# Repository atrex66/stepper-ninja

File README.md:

# stepper-ninja

An open-source, free, high-performance step generator, digital I/O, and PWM interface for LinuxCNC and Mach3.

**NEW — first version of the 3-axis Mach3 driver (USB):**
[StepperNinja Mach3 USB package](configurations/StepperNinja-Mach3-USB).
Includes Pico/Pico 2 firmware, the Windows plugin, machine profiles, and
[setup instructions](configurations/StepperNinja-Mach3-USB/README.en.md).

A separate **prototype Mach3 driver** is available for a fixed three-axis USB/UDP
firmware profile. LinuxCNC remains the default profile with flexible configuration.

You definitely do not need the official breakout board to use stepper-ninja. A cheap printer-port breakout board is enough, and other configurations are also possible.

## Documentation

- [Installation Guide](docs/INSTALL.md)
- [Configuration Guide](docs/CONFIG.md)
- [IP Configuration Guide](docs/IPCONFIG.MD)
- [Make Your Own Breakout Board](docs/MAKE-YOUR-OWN-BREAKOUTBOARD.md)
- [Mach3 prototype overview](docs/MACH3.en.md) ([Magyar](docs/MACH3.hu.md))
- [Mach3 build guide](docs/MACH3-BUILD.en.md) ([Magyar](docs/MACH3-BUILD.hu.md))
- [Mach3 protocol and execution reports](docs/MACH3-PROTOCOL.en.md)
- [Mach3 Feed Hold and G31](docs/MACH3-FEEDHOLD-G31.en.md)

## Languages

- [English](README.md)
- [Deutsch](README.de.md)
- [हिन्दी](README.hi.md)
- [Magyar](README.hu.md)
- [Português (Brasil)](README.pt-BR.md)

## LinuxCNC features

LinuxCNC supports quadrature encoders and spindle-synchronized motion, including threading. Encoder support is not implemented in the Mach3 driver.

- **Supported configurations**:

  - W5100S-evb-pico UDP Ethernet. <https://docs.wiznet.io/Product/iEthernet/W5100S/w5100s-evb-pico>
  - W5500-evb-pico (same as above)
  - W5100S-evb-pico2 (same as above)
  - W5500-evb-pico2 (same as above)
  - pico + W5500 module (needs the same wiring as the W5100S-evb-pico)
  - pico2 + W5500 module (if you use a pico2 board with 48 GPIO, you can use the extra GPIO now)
  - pico + Raspberry Pi4 (uses direct SPI connection, tested with the official LinuxCNC ISO, utilizes the extra GPIO from the Pi 4)
  - pico2 + Raspberry Pi4 (same as above)
  - pico + PI ZERO2W (uses SPI connection, LinuxCNC runs with linuxcncrsh, tested on Bookworm with patched kernel 6.13.2.5-rt5-v7+)
  - pico2 + PI ZERO2W (same as above, able to use the extra GPIO from the ZERO2W)
  - Stepper Ninja official breakout board (needs a pico and a W5500 module)

- **Using with single board compiters (SBC) and SPI**:
  - the stepper-ninja project now uses the kernel spi drivers and libgpiod v2 for communication, a littlebit slower
  - than the bmc2835 driver but with this change in theory no more barrier to use another SBC (single board computer) 

- **Breakout-board v1.0 - Digital version**: 16 optically isolated inputs, 8 optically isolated outputs, 4 step generators (differential output), 2 high-speed encoder inputs, 2 12-bit DAC outputs (unipolar).

- **step-generator**: max 8 with pico 1, max 12 with pico2. 1 MHz per channel. Pulse width is set from a HAL pin (96 ns - 6300 ns with a 125 MHz pico, 60 ns - 4000 ns with a 200 MHz pico).

- **quadrature-encoder**: max 8 with pico1, max 12 with pico2. High speed, zero-pulse handling, velocity estimation for low-resolution encoders, and spindle-synchronized motion support.

- **digital I/O**: you can configure the free pins of the pico as inputs and outputs.

- **PWM**: you can configure up to 16 GPIOs for PWM output (1900 Hz with 16-bit resolution up to 1 MHz with 7-bit resolution), and you can choose active-low or active-high behavior.

- **Software**:
  - LinuxCNC HAL driver supporting multiple instances (max 4), with safety functions (timeout, data checks).

- **extra I/O**: the I/O expander for the breakout board supports up to 64 inputs and 32 outputs total (with 3 expanders, 24 V optically isolated).

- **user breakout board code**: breakoutboard_user.c and breakoutboard_hal_user.c were added to the modules directory for makers to make integration easier.

- **sample KiCad breakout board**: a simple, low-cost DIY breakout board KiCad project is available in `configurations/RaspberryPi`. It connects a Pico/Pico2 to a Raspberry Pi via SPI and requires only a Pico or Pico2, a standard 40-pin GPIO header, and 2.54 mm PCB screw terminals.

- **supporters**: all active sponsors at or above $15 get access to the private breakout board repository for personal use, including production files such as Gerbers, BOM, and component positions.

- **Open-Source**: code and docs under MIT License.

## Mach3 prototype driver

The `mach3-driver/` directory contains a Mach3 SDK adapter and a portable
controller/client core. Select `STEPPER_NINJA_PROFILE=mach3-3axis` when building
the matching firmware. This profile has a fixed pinout: three STEP/DIR axes,
seven digital inputs, six digital outputs, and one spindle PWM output.

Implemented in the prototype:

- Buffered 1 ms XYZ motion and execution reports from physical STEP counts.
- Local acceleration-limited jog, homing, and dwell.
- Digital I/O, spindle RUN/DIR/PWM, and coolant outputs.
- Sessions, ACKs, duplicate-request suppression, watchdog, E-stop and limit handling.
- A Mach3 configuration dialog for IP/port, timing, polarity, and homing settings.
- Native Mach3 Feed Hold forwarding the planned braking trajectory; Cycle Start
  forwards Mach3's new startup trajectory.
- Coordinated G31 with separate contact and stopping positions, missed-contact
  detection, and controlled cancellation.

**Prototype status:** portable Linux tests cover motion, reports, and UDP behavior;
these use a substitute Mach3 planner. I have verified on Windows that USB STEP outputs and inputs work from Mach3 with the prebuilt driver and firmware.
Full Mach3 Feed Hold/G31 integration and hardware timing still need validation.
USB CDC motion transport is implemented with automatic console handover; full
Windows and physical machine validation remain pending. The Mach3 profile has no encoder; the LinuxCNC
performance and configuration features listed above do not describe its limits.
Motion protocol version 3 requires matching Mach3 driver and firmware builds.
The Pico firmware can also be built natively on Windows; no Linux machine is
required to build the firmware and Mach3 DLL. Once real Mach3 and hardware
testing has confirmed reliable operation, a release is planned with prebuilt
firmware and driver binaries. That validated release is not available yet.

[Mach3 USB configuration directory — prebuilt driver, firmware, and machine profiles](configurations/StepperNinja-Mach3-USB).

See the [English build guide](docs/MACH3-BUILD.en.md) or
[Hungarian build guide](docs/MACH3-BUILD.hu.md). The separate Mach3 profile
preserves LinuxCNC's existing flexible configuration and protocol.

## Contributors

The LinuxCNC 2.9/2.10 HAL API compatibility patch is based on code by [Frederic Müller (FredericM88)](https://github.com/FredericM88) in [linuxcnc-sim](https://github.com/FredericM88/linuxcnc-sim/tree/42ef3723da83b8ed88c123138c60437093255a22/compat/stepper-ninja), adapted for this driver under the MIT license. See the [compatibility notes](hal-driver/hal-api-compatibility.md) and [original license](hal-driver/LICENSE.hal-compat.txt).

- **code**: atrex66, pippin88

- **testing**: Jimfong1, Griletos

- **supporters**: Griletos, Cofhal, Sunhapas, milhead2, vanOverload

- **known-ninjas**: Griletos, Cofhal, Sunhapas, milhead2, vanOverload, Player

## Discord

- Request a fresh Discord invite in Discussions.

## License

- The quadrature encoder PIO program uses BSD-3 license by Raspberry Pi (Trading) Ltd.
- The `ioLibrary_Driver` is licensed under the MIT License by Wiznet.

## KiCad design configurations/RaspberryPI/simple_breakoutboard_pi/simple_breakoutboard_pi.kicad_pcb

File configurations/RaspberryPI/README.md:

# Installation and Build Instructions for Stepper-Ninja (Raspberry Pi SPI)

This guide explains how to build **Stepper-Ninja** and the LinuxCNC HAL driver for Raspberry Pi Pico/Pico2 connected via **SPI** to a Raspberry Pi 4/5.

This version uses the **kernel SPI driver** (`spidev`) and **libgpiod v2** for communication — no bcm2835 library required.

Tested with Pico SDK 2.1.1, CMake 3.20.6, and GNU ARM Embedded Toolchain. See [Troubleshooting](#troubleshooting) for common issues.

---

## Prerequisites

Before building, install the following dependencies:

```bash
sudo apt update
sudo apt install cmake gcc-arm-none-eabi binutils-arm-none-eabi \
                 build-essential unzip libgpiod-dev
```

**Pico SDK (2.1.1)**:

```bash
git clone https://github.com/raspberrypi/pico-sdk
cd pico-sdk
git submodule update --init
export PICO_SDK_PATH=/path/to/pico-sdk
```

Add `PICO_SDK_PATH` to your shell profile (e.g., `~/.bashrc`).

---

## Cloning the Repository

```bash
git clone https://github.com/atrex66/stepper-ninja
cd stepper-ninja
```

---

## Raspberry Pi SPI Setup

Enable SPI in `/boot/firmware/config.txt`:

```
dtparam=spi=on
```

> **Note:** The previous bcm2835-based version required `spi=off`. This version uses the kernel `spidev` driver — SPI **must be enabled**.

---

## Building with CMake and Make

### 1. Copy the Raspberry Pi configuration

```bash
cd ~/stepper-ninja
cp configurations/RaspberryPI/config.h firmware/inc/
```

### 2. Create a Build Directory

```bash
cd firmware/
mkdir build && cd build
```

### 3. Configure CMake

- For **Pico**:

  ```bash
  cmake ..
  ```

- For **Pico2**:

  ```bash
  cmake -DBOARD=pico2 ..
  ```

### 4. Build the Project

```bash
make
```

This generates `stepper-ninja-picoX.uf2`.

### 5. Flash the Pico

- Connect the Pico in BOOTSEL mode (hold BOOTSEL, plug in USB).
- If you are using the pico with other firmware use flash_nuke to erase previous data from the flash memory.
- Copy the `.uf2` file to the Pico's mass storage device.
- The Pico reboots and runs the firmware.

---

### 6. Build the HAL driver

 - go to __~/stepper-ninja/hal-driver__
 - run __./install.sh__ or __./rip_install.sh__ depending on your LinuxCNC installation

## Pico2 Support

For a Pico2, ensure:

- The Raspberry Pi is properly wired (SPI pins, INT pin, power).
- Use `-DBOARD=pico2` in the CMake step.

## Installing the LinuxCNC HAL Driver

To integrate Stepper-Ninja with LinuxCNC:

1. **Install the HAL Driver**:

   ```bash
   cd hal-driver
   ./install.sh
   ```

2. **Create a HAL File** (e.g., `stepper-ninja.hal`):

   ```hal
   loadrt stepgen-ninja

   addf stepgen-ninja.0.watchdog-process servo-thread
   addf stepgen-ninja.0.process-send servo-thread
   addf stepgen-ninja.0.process-recv servo-thread

   net x-pos-cmd joint.0.motor-pos-cmd => stepgen-ninja.0.stepgen.0.command
   net x-pos-fb stepgen-ninja.0.stepgen.0.feedback => joint.0.motor-pos-fb
   net x-enable axis.0.amp-enable-out => stepgen-ninja.0.stepgen.0.enable
   ```

3. **Update the INI File** (e.g., `your_config.ini`):

   ```ini
   [HAL]
   HALFILE = stepper-ninja.hal

   [EMC]
   SERVO_PERIOD = 1000000
   ```

4. **Run LinuxCNC**:

   ```bash
   linuxcnc your_config.ini
   ```

---

## Troubleshooting

- **CMake Error: PICO_SDK_PATH not found**:
  Ensure `PICO_SDK_PATH` is set and points to the Pico SDK directory.
  
  ```bash
  export PICO_SDK_PATH=/path/to/pico-sdk
  ```

- **Missing pioasm/elf2uf2**:
  Build these tools in the Pico SDK:
  
  ```bash
  cd pico-sdk/tools/pioasm
  mkdir build && cd build
  cmake .. && make
  ```

- **UTF-8 BOM Errors** (e.g., `∩╗┐` in linker output):
  Use CMake 3.20.6 or add `-DCMAKE_UTF8_BOM=OFF`:
  
  ```bash
  cmake -DCMAKE_UTF8_BOM=OFF ..
  ```

- **HAL Driver Errors**:
  Check `dmesg` for UDP connection issues:
  
  ```bash
  dmesg | grep stepgen-ninja
  ```

For more help, share error logs on the [GitHub Issues page](https://github.com/atrex66/stepper-ninja/issues) or the [Reddit thread](https://www.reddit.com/r/hobbycnc/comments/1koomzu/).

---

## Community Notes

Thanks to the r/hobbycnc community for testing! Stepper-Ninja v1.0 is tagged as a stable release: <https://github.com/atrex66/stepper-ninja/releases/tag/v1.0>

This version switches from bcm2835 to kernel SPI (`spidev`) and libgpiod v2, making it compatible with a wider range of SBCs in the future.

For more information, see the main [README](../../README.md).

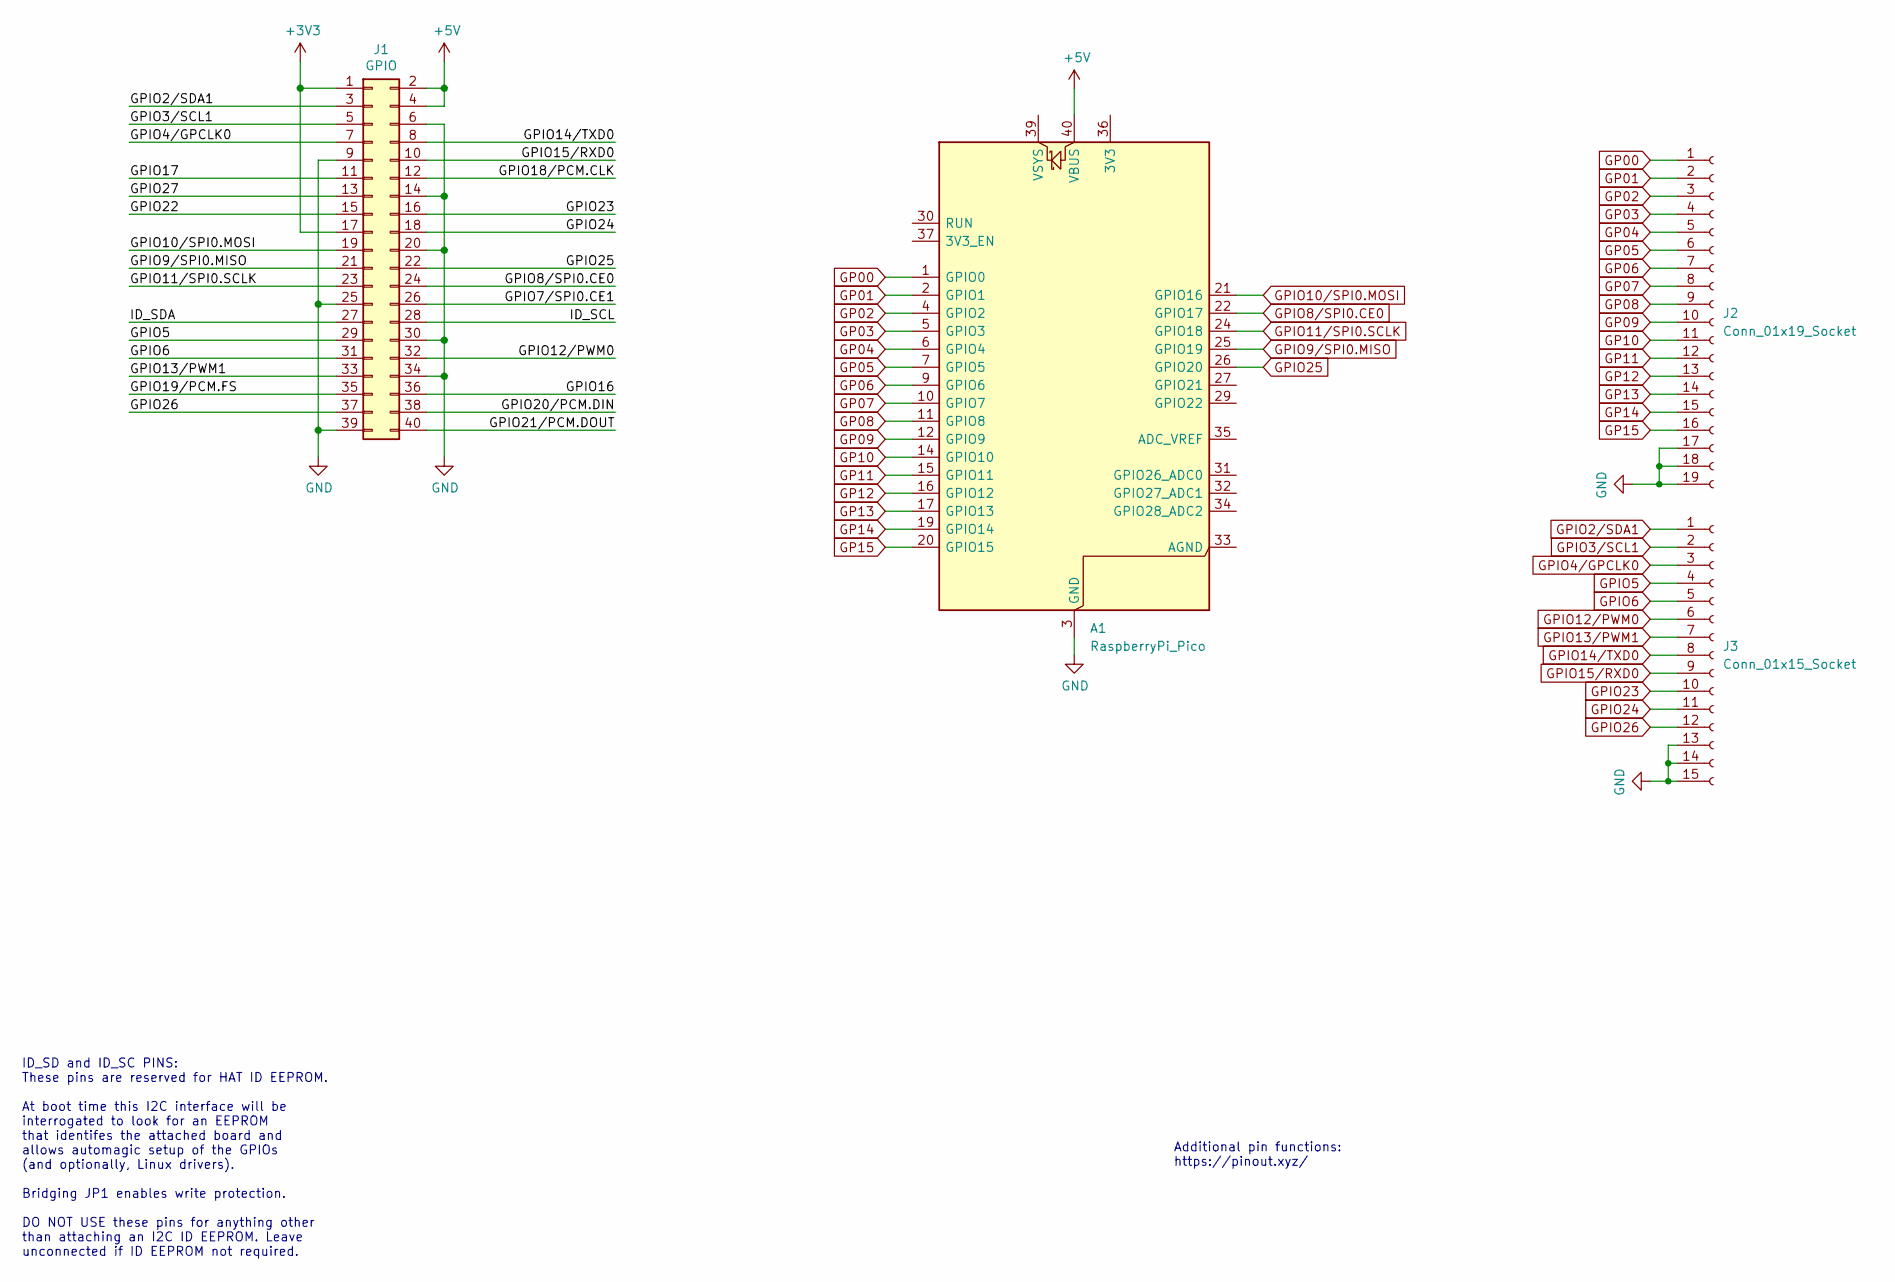
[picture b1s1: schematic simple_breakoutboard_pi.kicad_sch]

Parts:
A1: RaspberryPi_Pico; RaspberryPi_Pico_Common_Unspecified
J1: GPIO; PinSocket_2x20_P2.54mm_Vertical
J2: Conn_01x19_Socket; Molex_SL_171971-0019_1x19_P2.54mm_Vertical
J3: Conn_01x15_Socket; Molex_KK-254_AE-6410-15A_1x15_P2.54mm_Vertical

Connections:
+3V3: J1.1, J1.17
+5V: A1.40 (VBUS), J1.2, J1.4
/GPIO7/SPI0.CE1: J1.26
/GPIO16: J1.36
/GPIO17: J1.11
/GPIO18/PCM.CLK: J1.12
/GPIO19/PCM.FS: J1.35
/GPIO20/PCM.DIN: J1.38
/GPIO21/PCM.DOUT: J1.40
/GPIO22: J1.15
/GPIO27: J1.13
/ID_SCL: J1.28
/ID_SDA: J1.27
GND: A1.3 (GND), A1.8 (GND), A1.13 (GND), A1.18 (GND), A1.23 (GND), A1.28 (GND), A1.38 (GND), J1.6, J1.9, J1.14, J1.20, J1.25, J1.30, J1.34, J1.39, J2.17, J2.18, J2.19, J3.13, J3.14, J3.15
GP00: A1.1 (GPIO0), J2.1
GP01: A1.2 (GPIO1), J2.2
GP02: A1.4 (GPIO2), J2.3
GP03: A1.5 (GPIO3), J2.4
GP04: A1.6 (GPIO4), J2.5
GP05: A1.7 (GPIO5), J2.6
GP06: A1.9 (GPIO6), J2.7
GP07: A1.10 (GPIO7), J2.8
GP08: A1.11 (GPIO8), J2.9
GP09: A1.12 (GPIO9), J2.10
GP10: A1.14 (GPIO10), J2.11
GP11: A1.15 (GPIO11), J2.12
GP12: A1.16 (GPIO12), J2.13
GP13: A1.17 (GPIO13), J2.14
GP14: A1.19 (GPIO14), J2.15
GP15: A1.20 (GPIO15), J2.16
GPIO2/SDA1: J1.3, J3.1
GPIO3/SCL1: J1.5, J3.2
GPIO4/GPCLK0: J1.7, J3.3
GPIO5: J1.29, J3.4
GPIO6: J1.31, J3.5
GPIO8/SPI0.CE0: A1.22 (GPIO17), J1.24
GPIO9/SPI0.MISO: A1.25 (GPIO19), J1.21
GPIO10/SPI0.MOSI: A1.21 (GPIO16), J1.19
GPIO11/SPI0.SCLK: A1.24 (GPIO18), J1.23
GPIO12/PWM0: J1.32, J3.6
GPIO13/PWM1: J1.33, J3.7
GPIO14/TXD0: J1.8, J3.8
GPIO15/RXD0: J1.10, J3.9
GPIO23: J1.16, J3.10
GPIO24: J1.18, J3.11
GPIO25: A1.26 (GPIO20), J1.22
GPIO26: J1.37, J3.12

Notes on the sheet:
Additional pin functions: https://pinout.xyz/
ID_SD and ID_SC PINS: These pins are reserved for HAT ID EEPROM. At boot time this I2C interface will be interrogated to look for an EEPROM that identifes the attached board and allows automagic setup of the GPIOs (and optionally, Linux drivers). Bridging JP1 enables write protection. DO NOT USE th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

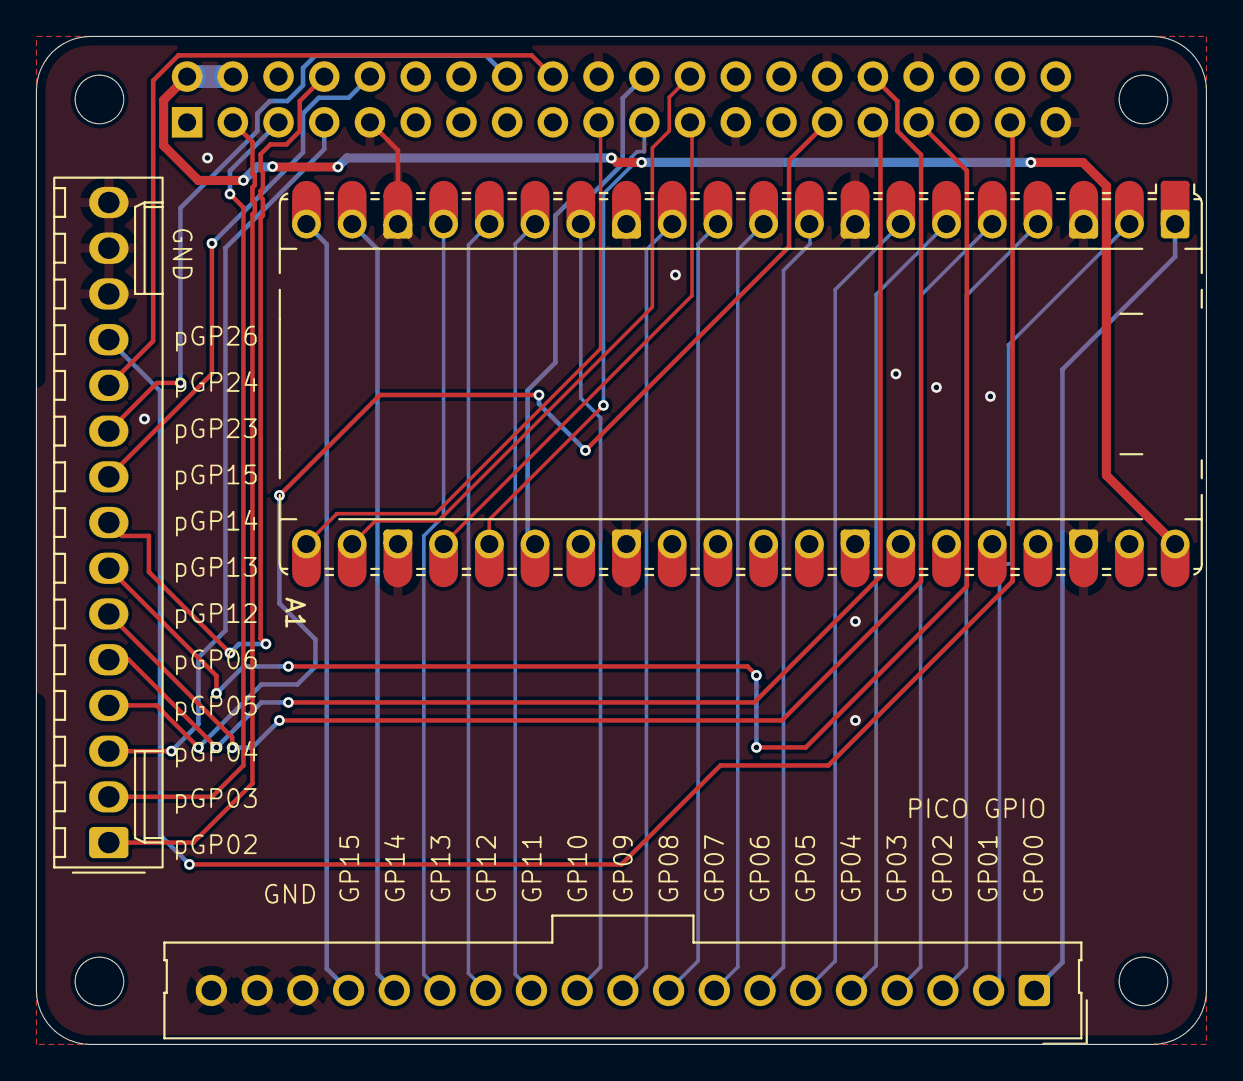
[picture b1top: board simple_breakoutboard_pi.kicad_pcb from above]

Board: 2 copper layers, 65.0 x 56.0 mm, 8 parts (1 on the bottom side), 36 nets.

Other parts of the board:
MH1, MH2, MH3, MH4: MountingHole_2.7mm_M2.5

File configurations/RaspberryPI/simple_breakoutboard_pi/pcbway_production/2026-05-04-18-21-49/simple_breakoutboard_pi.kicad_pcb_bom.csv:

Designator,Quantity,Value,Footprint,Package,MPN,DNP,Mount_Type,Description
A1,1,RaspberryPi_Pico,RaspberryPi_Pico_Common_Unspecified,,,,tht,"Versatile and inexpensive microcontroller module powered by RP2040 dual-core Arm Cortex-M0+ processor up to 133 MHz, 264kB SRAM, 2MB QSPI flash; also supports Raspberry Pi Pico 2"
J1,1,GPIO,PinSocket_2x20_P2.54mm_Vertical,,,,tht,"Generic connector, double row, 02x20, odd/even pin numbering scheme (row 1 odd numbers, row 2 even numbers), script generated (kicad-library-utils/schlib/autogen/connector/)"
J2,1,Conn_01x19_Socket,Molex_SL_171971-0019_1x19_P2.54mm_Vertical,,,,tht,"Generic connector, single row, 01x19, script generated"
J3,1,Conn_01x15_Socket,Molex_KK-254_AE-6410-15A_1x15_P2.54mm_Vertical,,,,tht,"Generic connector, single row, 01x15, script generated"

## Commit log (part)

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2025-05-15 Readme error fixed
2025-05-15 PINOUT added
2025-05-15 driver name fixed
2025-05-15 fixed max instances
2025-05-15 added placeholder for docs
2025-05-15 added precompiled binary
2025-05-15 added LICENSE.TXT for quadrature_encoder.pio program
2025-05-15 Added config description, generated with AI
2025-05-15 fixed descriptions and serial terminal start, generated with AI
2025-05-15 fixed serial device address
2025-05-15 added picture of w5100s-evb-pico
2025-05-15 Image of w5100s-evb-pico
2025-05-15 fixed misplaced #include file
2025-05-16 fix missing feedback signal
2025-05-16 updated binary
2025-05-16 added velocity mode to stepgens
2025-05-16 fixed timing for support not only 1mS servo thread in stepgen velocity mode
2025-05-17 changes for work with Wiznet W5500
2025-05-17 default terminal init screen added
2025-05-17 Added test configuration for the hal module
2025-05-17 added build documentation
2025-05-17 changed hal example
2025-05-18 added separete prebuild uf2 for w5100s and w5500
2025-05-18 added discord server address and temporary removed w5500 support from INSTALL.md
2025-05-19 Fixed text to match markdown rules
2025-05-19 updated .gitignore
2025-05-20 fix for jmfong to play with W5500. :)
2025-05-20 Temporary fix for W5500
2025-05-20 added utilities
2025-05-20 added build W5500
2025-05-20 fixed misspelling in hal section
2025-05-21 added checksum checking to flash stored data
2025-05-21 removed not used code
2025-05-21 added W5500 + pico to supported boards
2025-05-21 changed calculation of timing
2025-05-21 high pulse width corrected to 3uS
2025-05-21 added pulse width changing under development
2025-05-22 added dinamic pulse width setting to stepgen
2025-05-22 added changes to the README
2025-05-22 latest version 2025.May.22
2025-05-23 added hal pin descriptions
2025-05-23 added debug pins
2025-05-23 more pulse width settings, benchmark automatch with the current config
2025-05-23 last build 2025.may.23
2025-05-23 WIZCHIP_TYPE added to uf2 name
2025-05-23 2025.may.23
2025-05-23 updated timing
2025-05-23 removed not used variables
2025-05-23 fixed image name
2025-05-23 cranked up to 512 steps/servo cycle
2025-05-24 removed python files
2025-05-24 added debug info
2025-05-25 transmission.h and transmission.c for easy packet modification'
2025-05-25 removed ascii art
2025-05-25 added free pins as inputs with pullups
2025-05-25 added inputs outputs pwm
2025-05-25 Configuration update
2025-05-25 hal pins updated
2025-05-25 replaced binary
2025-05-25 prebuilt with the new configuration
2025-05-25 changed text to represent the configuration
2025-05-25 added min-limit pin
2025-05-25 added pwm.min-limit pin description
2025-05-25 fixing outputs
2025-05-25 another error fixed with the outputs
2025-05-25 updated binaries 2025.may.25 22:16 Budapest time
2025-05-25 fixed gp15 not working
2025-05-26 moved configurations to config.h
2025-05-26 Update 2025.may.26 22:58
2025-05-26 adding inverting pwm to the config
2025-05-27 updated hal examples 2025.may.27 10:31
2025-05-27 fixed bug with the encoder numbers
2025-05-27 Binary update 2025.may.27 10:41
2025-05-27 Update firmware binaries for W5100S and W5500 on
2025-05-27 1024 step / servo cycle
2025-05-27 fixed missing symbol link
2025-05-27 added independent timer interrupt to step generation
2025-05-28 added step counter, fixed input and output definitions
2025-05-28 config revert
2025-05-29 removed unused code
2025-05-30 readme update
2025-05-31 fixed arm crosscompiler installation instructions
2025-05-31 form corrected
2025-05-31 updated CMakeLists.txt for the counters
2025-05-31 fixed bug preventing build of the counter
2025-05-31 ignored local file
2025-06-02 new image added from the breakout board PCB
2025-06-04 Added possibility to invert step pins
2025-06-04 mofified buildall to push to test
2025-06-04 config.h generator for easy configuration
2025-06-05 stepgen rounding bug fixed.
2025-06-05 zero crossing bug fix
2025-06-05 reset all button not working fixed
2025-06-05 Ability to change the active level
2025-06-06 added features list
2025-06-06 readme updated
2025-06-06 ignored __pycache__
2025-06-06 removed __pychache__ directory
2025-06-06 revork root directory structure
2025-06-06 removed pio_settings.h from root directory
2025-06-06 added description to the spindle.index-enable
2025-06-06 added different predefined configurations
2025-06-06 Readme added to configurations
2025-06-06 replaced virtual serial port initialisation, with the allocation of the rx and tx buffer because of no sense to printf before init
2025-06-10 Discord server address updated
2025-06-11 reorganized file structure
2025-06-11 modified cmakelists.txt to support pico2 build, added sudo to sterminal.sh to easy use not need to setup dialup group
2025-06-16 first iteration to the RPI4 codebase
2025-06-16 rpi4 support in the hal driver
2025-06-16 pinout connection for the rapsberry Pi4/5 version
2025-06-17 changes made in config need changes on the hal driver
2025-06-17 config.h default to etherent
2025-06-17 added pullup setup for the input pins
2025-06-17 added local files to the .gitignore
2025-06-17 changed html configurator, do not use only a sample in this stage
2025-06-17 cleanup the config.h and added pin aliases to the GPIO numbers
2025-06-17 new configuration, old ones deleted not fit to the current config.h now you can disable all encoders if you want
2025-06-17 changes to more understadable the config
2025-06-17 correction
2025-06-17 changed all gpio in the config to pins.
2025-06-17 misplaced pin
2025-06-18 added chinese breakoutboard configuration and wiring
2025-06-18 picture of the bob
2025-06-18 added -DBOARD=pico2 to the cmake file for easy build
2025-06-18 new features
2025-06-18 chinese breakoutboard readme
2025-06-18 chinese breakoutboard readme added info for wiring
2025-06-18 fixing errors related to rpi version
2025-06-18 rpi related fix
2025-06-18 debug info added
2025-06-18 csak
2025-06-19 Update main.c
    removed pullup from the inputs.
2025-06-19 Update config.h
    added option to use pullups on the inputs
2025-06-19 Update main.c
    following the new config changes
2025-06-19 Multple PWM generation
2025-06-19 chinese mreakout board changes related to multiple PWM channel use
2025-06-19 misplaced config fix
2025-06-20 Solved the w5500 interrupt initialization problem, w5500 and w5100s communication now utilizing the INT pin
2025-06-21 fixed dir pins def bug
2025-06-21 fixed timeout not triggering
2025-06-22 proper encoder-index handling updated to work as LiniuxCNC requires
2025-06-22 updated readme and install.md
2025-06-22 updated hal-pins.md (encoder signals added)
2025-06-22 pico2 extra pio utilization added
2025-06-23 changes made the config affecting the configurations are fixed, picobob-dlx and chinese breakout board"
2025-06-23 fix to the hal driver properly handle the encoders=0
2025-06-23 separeted internal config to footer.h
2025-06-23 added ability to overclock the pico
2025-06-23 fixed text output showing wrong timing
2025-06-23 changed maximum value for the pulse width search
2025-06-23 fixed w5100s interrupt init
2025-06-25 rpi4 spi version fixes, more coming
2025-06-25 default configuration disabled the raspi4 spi communication
2025-06-25 added readme to rpi4 config
2025-06-25 fixed repository name in the rpi4 readme.md
2025-06-25 added step to the installation, copy the raspberry pi4 config file
2025-06-26 changes in the readme and pi4 configuration
2025-06-27 fix for pico2 48GPIO
2025-06-27 another fix, i missed the indexing
2025-06-27 fix of (gpio48) outputs, hal-driver side
2025-06-30 now you can define 0 stepgens
2025-06-30 fix for GPIO > 31
2025-07-05 benchmark bynari added to gitignore
2025-07-05 implemented the MCP4725 DAC and adjusted the breakout board code
2025-07-06 Update config.h
    Fixed breakout_board typo
2025-07-06 Update picoBOB-DLX.h
    Fixed breakout_board typo
2025-07-06 Update main.h
    Fixed breakout_board typo
2025-07-06 Update main.c
    Fixed breakout_board typo
2025-07-06 added code of conduct, removed _receive() argument what generated warning.
2025-07-06 updated code_of_conduct
2025-07-06 added code of conduct
2025-07-06 various updates, picture of the bob and tried add pulldown, but not working pico-sdk issue.
2025-07-06 added pwm programmers model picture
2025-07-06 drawings for the breakout board
2025-07-17 fix for inputs on breakout board
2025-07-17 fixed wrong variable type
2025-07-18 network settings migrated to config.h, input_buffer get the new value in one step preventing false data in the tx buffer (pico side)
2025-07-21 readme updates
2025-07-21 updated readme and different configs for the last update
2025-07-22 added dedicated config for the V1.0 Digital breakout board
2025-07-29 early version of configurator
2025-07-29 added cached python files
2025-07-29 progress in the configurator
2025-07-29 added functions to configurator
2025-07-29 more config tool updates
2025-07-30 configurator progress
2025-07-30 little fixes for configurator
2025-07-30 new node WeActRP2350B, little fixes
2025-08-01 fresh discord link, progress with the configurator
2025-08-01 encoder velocity estimation implementation
2025-08-02 fixed encoder velocity, added latched pins to the encoder component
2025-08-04 adjusted lowpass filter, added new picture, updated README'
2025-08-05 added 3d render of the io expander
2025-08-05 changes in the readme
2025-08-09 added io_expanders support code
2025-08-12 new picture of a fully populated breakout board
2025-08-13 fixed config collosion with the breakout board settings
2026-02-25 Initial plan
2026-02-25 Add Pico device name parameter and feature set to discovery protocol with automatic HAL pin creation
2026-02-25 Update documentation to reflect auto-discovery, device naming, and runtime HAL pin allocation
2026-02-25 Add device name to flash config and serial terminal name command
2026-04-04 added separated languages for install.md ipconfig.md and make-your-own-breakoutboard.md, added working-principles.md to the doc
2026-04-04 encoder.velocity patch
2026-04-05 added test program for the breakoutboard
2026-04-07 rollback to the original driver name stepgen-ninja for compatibility with older version
2026-04-07 rollback to stepgen-ninja driver name in all text
2026-04-07 CMakeLists.txt update
2026-04-08 Breakoutboard v1.0 test program added
2026-04-08 generated doc for the breakoutboard test program
2026-04-13 added selectable stepgen buffering to eliminate linuxcnc latency issues, added encoder pio selector, SUBSTEP or LEGACY the ability of use the old encoder pio program
2026-04-15 fixed an rpi frame length bug that prevents communication on spi because of different rx and tx frame size
2026-04-15 raspberry_pi_spi reverted to 0 by default
2026-04-17 default config fixed
2026-05-03 Cleaned unneccessary files
2026-05-03 HAL:Migrated to kernel SPI drivers and libgpiod v2 for compatibility
2026-05-03 Moved PI pin definitions to the config.h
2026-05-03 updated raspberry pi readme.md to reflect the changes
2026-05-04 Raspberry pi SPI install script and sample linuxcnc configuration
2026-05-04 removed raspberry pico detection
2026-05-04 Fixed new line in the pico selection
2026-05-04 Added user addition to the gpio and the spi group
2026-05-04 Added simple breakout board for the raspberry pi directory (SPI)
2026-05-04 readme updated for the diy breakout board
2026-05-07 Direction pin init fixed in main.c
2026-05-07 Fixed inverted raspberry inpiuts in stepgen-ninja.c
2026-05-11 False comment fixed on the config.h, only the gp20 are freeing when using SPI communication
2026-05-11 removed the direct text comments because it is misleading, and added a pdf link instead
2026-05-14 Changed milltask polling rate to 0.01s
2026-05-14 Step generator setting dormant_cycles reverted back to 6, general setting for buffered/unbuffered step generation
2026-05-17 Readme.md shortened
2026-05-17 PicoBOC-DLX config updated
2026-05-17 Install.md shortened
2026-05-17 Bad definition fixed STEP/DIR define
